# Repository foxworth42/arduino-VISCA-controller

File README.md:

# Arduino VISCA Controller

## The project is a work-in-progress

This is a project for using an Arduino to send VISCA commands.  This is tailored for interfacing with the
Cisco TelePresence PrecisionHD series of conference cameras (specifically testing with the TTC8-02 12x zoom w/ SDI output).

The TelePresence cameras have a slight quirk to controlling it over VISCA.  To get manual control over the pan/tilt/zoom
rates the camera needs to be sent the IR disable command, otherwise all movements behave with a speed ramp as if you 
were controlling it with an IR remote.

The Arduino Shield board present in the EAGLE directory is intended to make connecting to a TelePresence camera and
wiring I/O easier.  The shield has headers to allow for powering the Arduino off its internal voltage regulator or via
VIN (includes header points to make swapping easy).  There is also a header to provide 12v power over the RJ45
connection to remotely power the camera.  The shield incudes an RS232 transciever so it is ready to plug into the
camera's control port with a standard ethernet cable.

[Cisco TelePresence PrecisionHD User Guide](https://www.cisco.com/c/dam/en/us/td/docs/telepresence/endpoint/camera/precisionhd/user_guide/precisionhd_1080p-720p_camera_user_guide.pdf) (includes supported VISCA command details, cable wiring, etc.)

# Arduino Shield components

|Component|Quantity|Notes|Link|
|---|---|---|---|
|Arduino Shield|1|See EAGLE directory|[Link](https://oshpark.com/shared_projects/oP5dpPBc)|
|RS232 Transciever|1| |[Link](https://www.mouser.com/ProductDetail/968-HIN202IBNZ-T/)|
|0.1uf SMD Capacitor|5| |[Link](https://www.mouser.com/ProductDetail/80-C0805C104J5R/)|
|RJ45 Jack|1| |[Link](https://www.mouser.com/ProductDetail/523-RJHSE-5381/)|
|2pin Molex Header|2|Or whatever header you prefer|[Link](https://www.mouser.com/ProductDetail/538-22-23-2021/)|
|2pin Molex Housing|2| |[Link](https://www.mouser.com/ProductDetail/538-22-01-3027/)|
|3pin Molex Header|4| |[Link](https://www.mouser.com/ProductDetail/538-22-23-2031/)|
|3pin Molex Housing|4| |[Link](https://www.mouser.com/ProductDetail/538-22-01-3037/)|
|4pin Molex Header|2| |[Link](https://www.mouser.com/ProductDetail/538-22-23-2041/)|
|4pin Molex Housing|2| |[Link](https://www.mouser.com/ProductDetail/538-22-01-3047/)|
|8pin Molex Header|2| |[Link](https://www.mouser.com/ProductDetail/538-22-23-2081/)|
|8pin Molex Housing|2| |[Link](https://www.mouser.com/ProductDetail/538-22-01-3087/)|
|Crimp contacts for Molex housings|Lots| |[Link](https://www.mouser.com/ProductDetail/538-08-51-0108-LP/)|
|Crimp tool for Molex contacts|1| |[Link](https://www.amazon.com/gp/product/B078WPT5M1/ref=ppx_yo_dt_b_search_asin_title?ie=UTF8&psc=1)|
|Bunch of single row 2.54 pitch pin headers|Bunch| | |
|10k Ohm Resistors|10| |

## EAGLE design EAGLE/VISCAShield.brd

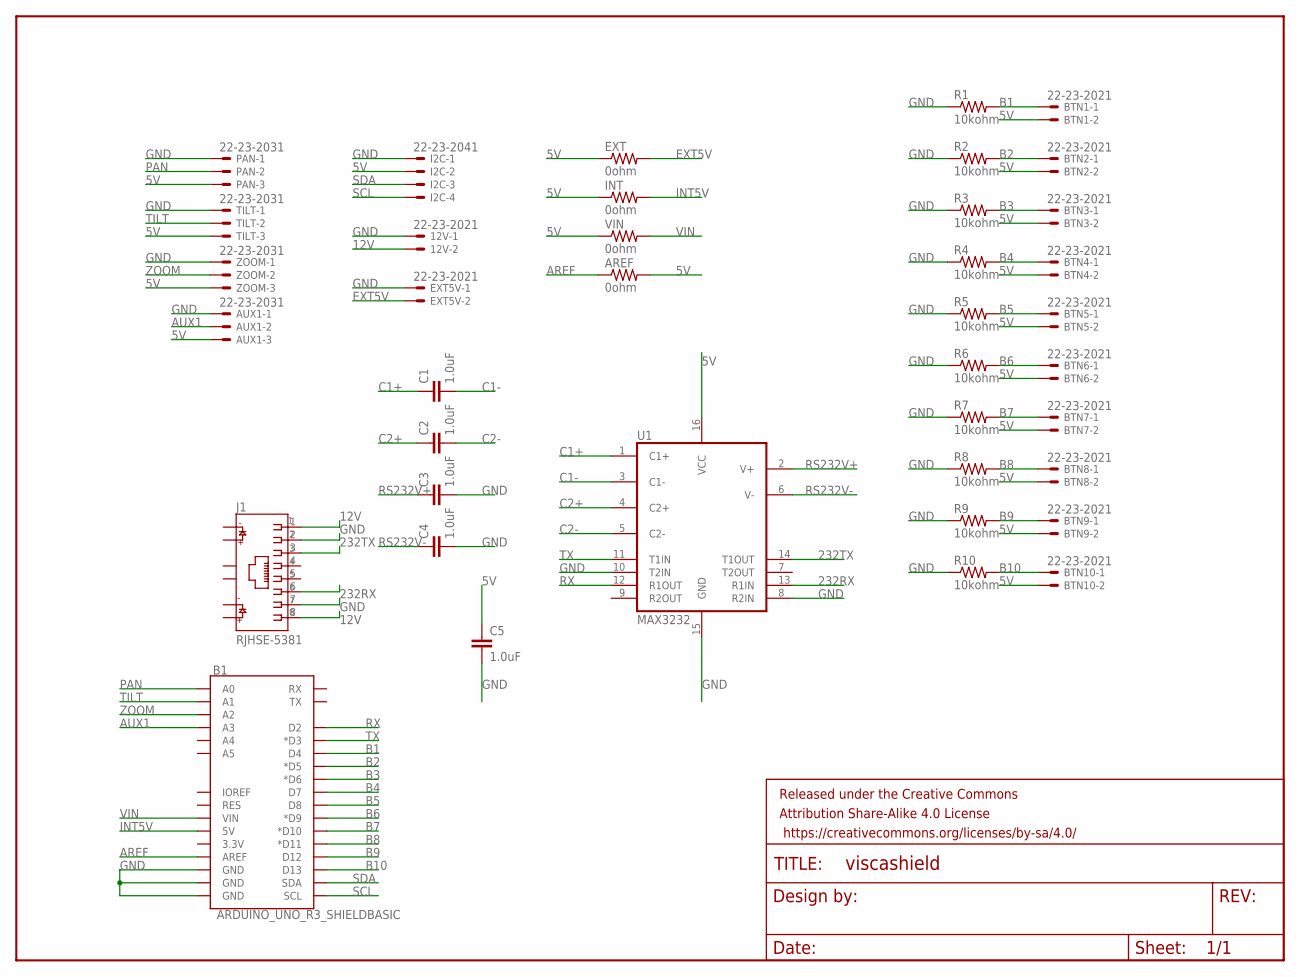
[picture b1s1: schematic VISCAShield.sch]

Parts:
12V: 22-23-2021
AREF: 0ohm; 0204V
AUX1: 22-23-2031
B1: ARDUINO_UNO_R3_SHIELDBASIC; UNO_R3_SHIELD
BTN1, BTN2, BTN3, BTN4, BTN5, BTN6, BTN7, BTN8, BTN9, BTN10: 22-23-2021
C1, C2, C3, C4, C5: 1.0uF; 0805
EXT: 0ohm; 0204V
EXT5V: 22-23-2021
FRAME1: FRAME-LETTERNO_PACKAGE; DUMMY
I2C: 22-23-2041
INT: 0ohm; 0204V
J1: RJHSE-5381; AMPHENOL_RJHSE-5381
PAN: 22-23-2031
R1, R2, R3, R4, R5, R6, R7, R8, R9, R10: 10kohm; 0204V
TILT: 22-23-2031
U1: MAX3232; SO16
VIN: 0ohm; 0204V
ZOOM: 22-23-2031

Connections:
5V: AREF.2, AUX1.3, BTN1.2, BTN2.2, BTN3.2, BTN4.2, BTN5.2, BTN6.2, BTN7.2, BTN8.2, BTN9.2, BTN10.2, C5.1, EXT.1, I2C.2, INT.1, PAN.3, TILT.3, U1.16 (VCC), VIN.1, ZOOM.3
12V: 12V.2, J1.1, J1.8
232RX: J1.6, U1.13 (R1IN)
232TX: J1.3, U1.14 (T1OUT)
AREF: AREF.1, B1.AREF
AUX1: AUX1.2, B1.A3
B1: B1.D4, BTN1.1, R1.2
B2: B1.D5 (*D5), BTN2.1, R2.2
B3: B1.D6 (*D6), BTN3.1, R3.2
B4: B1.D7, BTN4.1, R4.2
B5: B1.D8, BTN5.1, R5.2
B6: B1.D9 (*D9), BTN6.1, R6.2
B7: B1.D10 (*D10), BTN7.1, R7.2
B8: B1.D11 (*D11), BTN8.1, R8.2
B9: B1.D12, BTN9.1, R9.2
B10: B1.D13, BTN10.1, R10.2
C1+: C1.1, U1.1 (C1+)
C1-: C1.2, U1.3 (C1-)
C2+: C2.1, U1.4 (C2+)
C2-: C2.2, U1.5 (C2-)
EXT5V: EXT.2, EXT5V.2
GND: 12V.1, AUX1.1, B1.GND@0 (GND), B1.GND@1 (GND), B1.GND@2 (GND), C3.2, C4.2, C5.2, EXT5V.1, I2C.1, J1.2, J1.7, PAN.1, R1.1, R2.1, R3.1, R4.1, R5.1, R6.1, R7.1, R8.1, R9.1, R10.1, TILT.1, U1.8 (R2IN), U1.10 (T2IN), U1.15 (GND), ZOOM.1
INT5V: B1.5V, INT.2
PAN: B1.A0, PAN.2
RS232V+: C3.1, U1.2 (V+)
RS232V-: C4.1, U1.6 (V-)
RX: B1.D2, U1.12 (R1OUT)
SCL: B1.SCL, I2C.4
SDA: B1.SDA, I2C.3
TILT: B1.A1, TILT.2
TX: B1.D3 (*D3), U1.11 (T1IN)
VIN: B1.VIN, VIN.2
ZOOM: B1.A2, ZOOM.2

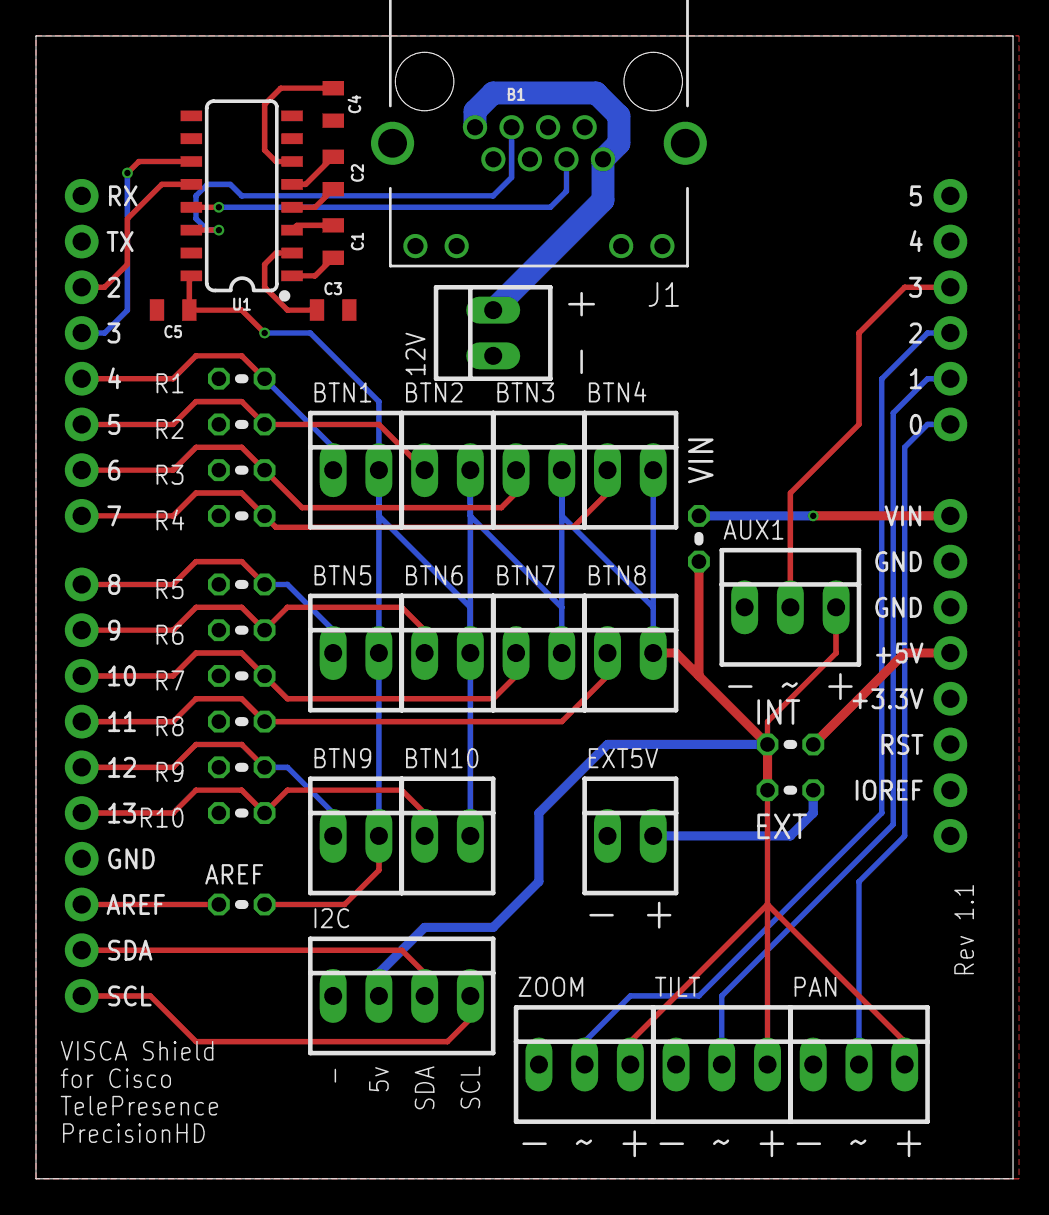
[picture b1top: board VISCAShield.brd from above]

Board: 2 copper layers, 54.3 x 63.5 mm, 40 parts (0 on the bottom side), 33 nets.

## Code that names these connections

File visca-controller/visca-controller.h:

#ifndef VISCACONTROLLER
#define VISCACONTROLLER

#include <Arduino.h>
#include <EEPROM.h>
//#include <LiquidCrystal_I2C.h>
#include <SoftwareSerial.h>

// Pin assignments from arduno shield.

// Analog inputs
#define PAN 0
#define TILT 1
#define ZOOM 2
#define AUX1 3
#define AUX2 4
#define AUX3 5

// Serial I/O for VISCA
#define VISCARX 2
#define VISCATX 3

// Button inputs
#define BTN1 4
#define BTN2 5
#define BTN3 6
#define BTN4 7
#define BTN5 8
#define BTN6 9
#define BTN7 10
#define BTN8 11
#define BTN9 12
#define BTN10 13
int buttons[] = {
  BTN1,
  BTN2,
  BTN3,
  BTN4,
  BTN5,
  BTN6,
  BTN7,
  BTN8,
  BTN9,
  BTN10
};


const byte numChars = 16;
byte viscaMessage[numChars];

byte buttonPreviousStatus = 0x00;
byte buttonCurrentStatus = 0x00;

// Pan/Tilt
byte panTilt[9] =       { 0x81, 0x01, 0x06, 0x01, 0x00, 0x00, 0x03, 0x03, 0xFF };
byte panUp[9] =         { 0x81, 0x01, 0x06, 0x01, 0x00, 0x00, 0x03, 0x01, 0xFF }; // 8x 01 06 01 0p 0t 03 01 ff
byte panDown[9] =       { 0x81, 0x01, 0x06, 0x01, 0x00, 0x00, 0x03, 0x02, 0xFF }; // 8x 01 06 01 0p 0t 03 02 ff
byte panLeft[9] =       { 0x81, 0x01, 0x06, 0x01, 0x00, 0x00, 0x01, 0x03, 0xFF }; // 8x 01 06 01 0p 0t 01 03 ff
byte panRight[9] =      { 0x81, 0x01, 0x06, 0x01, 0x00, 0x00, 0x02, 0x03, 0xFF }; // 8x 01 06 01 0p 0t 02 03 ff
byte panUpLeft[9] =     { 0x81, 0x01, 0x06, 0x01, 0x00, 0x00, 0x01, 0x01, 0xFF }; // 8x 01 06 01 0p 0t 01 01 ff
byte panUpRight[9] =    { 0x81, 0x01, 0x06, 0x01, 0x00, 0x00, 0x02, 0x01, 0xFF }; // 8x 01 06 01 0p 0t 02 01 ff
byte panDownLeft[9] =   { 0x81, 0x01, 0x06, 0x01, 0x00, 0x00, 0x01, 0x02, 0xFF }; // 8x 01 06 01 0p 0t 01 02 ff
byte panDownRight[9] =  { 0x81, 0x01, 0x06, 0x01, 0x00, 0x00, 0x02, 0x02, 0xFF }; // 8x 01 06 01 0p 0t 02 02 ff

byte panStop[9] =       { 0x81, 0x01, 0x06, 0x01, 0x09, 0x09, 0x03, 0x03, 0xFF }; // Camera Stop
byte panTiltPosReq[5] = { 0x81, 0x09, 0x06, 0x12, 0xff }; // Resp: y0 50 0p 0q 0r 0s 0t 0u 0v 0w ff ; pqrs: pan position ; tuvw: tilt position

// Zoom
// Tele: 8x 01 04 07 2p ff 
// Wide: 8x 01 04 07 2p ff 
byte zoom[6] =    { 0x81, 0x01, 0x04, 0x07, 0x2F, 0xff }; // 8x 01 04 07 2p ff 
byte zoomTele[6] =    { 0x81, 0x01, 0x04, 0x07, 0x2F, 0xff }; // 8x 01 04 07 2p ff 
byte zoomWide[6] =    { 0x81, 0x01, 0x04, 0x07, 0x3F, 0xff }; // 8x 01 04 07 3p ff
byte zoomStop[6] =    { 0x81, 0x01, 0x04, 0x07, 0x00, 0xff };
byte zoomDirect[9] =  { 0x81, 0x01, 0x04, 0x47, 0x00, 0x00, 0x00, 0x00, 0xff }; // 8x 01 04 47 0p 0q 0r 0s ff pqrs: zoom position
byte zoomPosReq[5] =  { 0x81, 0x09, 0x04, 0x47, 0xff }; // Resp: y0 50 0p 0q 0r 0s ff 


// Focus
byte focusAuto[6] =     { 0x81, 0x01, 0x04, 0x38, 0x02, 0xff };
byte focusManual[6] =   { 0x81, 0x01, 0x04, 0x38, 0x03, 0xff };
byte focusDirect[9] =   { 0x81, 0x01, 0x04, 0x48, 0x00, 0x00, 0x00, 0x00, 0xff }; // 8x 01 04 48 0p 0q 0r 0s ff pqrs: focus position
byte focusFar[6] =      { 0x81, 0x01, 0x04, 0x08, 0x20, 0xff };
byte focusNear[6] =     { 0x81, 0x01, 0x04, 0x08, 0x30, 0xff };
byte focusStop[6] =     { 0x81, 0x01, 0x04, 0x08, 0x00, 0xff };
byte focusModeInq[5] =  { 0x81, 0x09, 0x04, 0x38, 0xff }; // Resp: y0 50 0p ff ; p=2: Auto, p=3: Manual

// Iris / Gain
byte aeAuto[6] =      { 0x81, 0x01, 0x04, 0x39, 0x00, 0xff };
byte aeManual[6] =    { 0x81, 0x01, 0x04, 0x39, 0x03, 0xff };
byte irisDirect[9] =  { 0x81, 0x01, 0x04, 0x4B, 0x00, 0x00, 0x00, 0x00, 0xff }; // 8x 01 04 4B 0p 0q 0r 0s ff pqrs: Iris position, range 0..50
byte gainDirect[9] =  { 0x81, 0x01, 0x04, 0x4C, 0x00, 0x00, 0x00, 0x00, 0xff }; // 8x 01 04 4c 0p 0q 0r 0s ff pqrs: Gain position, values: 12-21dB.
byte aeModeInq[5] =   { 0x81, 0x09, 0x04, 0x39, 0xff }; // Resp: y0 50 0p ff ; p=0: Auto, p=3: Manual

// White Balance
byte wbAuto[6] =        { 0x81, 0x01, 0x04, 0x35, 0x00, 0xff };
byte wbTableManual[6] = { 0x81, 0x01, 0x04, 0x35, 0x06, 0xff };
byte wbTableDirect[9] = { 0x81, 0x01, 0x04, 0x75, 0x00, 0x00, 0x0, 0x00, 0xff }; // 8x 01 04 75 0p 0q 0r 0s ff pqrs = wb table.

// Config
byte address_command[4] = { 0x88, 0x30, 0x01, 0xFF }; // Sets camera address (Needed for Daisy Chaining)
byte if_clear[5] =        { 0x88, 0x01, 0x00, 0x01, 0xFF }; // Checks to see if communication line is clear
byte ir_off[6] =          { 0x81, 0x01, 0x06, 0x09, 0x03, 0xff }; // Turn off IR control (required for speed control of Pan/Tilt on TelePresence cameras)
byte callLedOn[6] =     { 0x81, 0x01, 0x33, 0x01, 0x01, 0xff};
byte callLedOff[6] =    { 0x81, 0x01, 0x33, 0x01, 0x00, 0xff};
byte callLedBlink[6] =  { 0x81, 0x01, 0x33, 0x01, 0x02, 0xff};

int delayTime = 500;  //Time between commands

void sendViscaPacket(byte* packet, int byteSize, bool echoCommand = true, bool sendPacket = true);

#endif

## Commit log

2020-01-04 Initial commit of arduino shield design.
    VISCA shield that exposes all pins to headers ready to be wired to 10 buttons,
    6 pots, I2C, with the option for external 5v, as well as an RJ45 jack wired
    for connecting to Cisco PrecisionHD PTZ cameras.
2020-01-04 initial commit of arduino sketch for VISCA controller.
2020-01-04 Add some quick comments about what the definitions are for.
2020-01-12 Some revisions.
2020-01-12 Remove I2C display for now until I start to make use of it.
2020-01-12 Add more axid movements, add focus control.
2020-01-12 Change return back.
2020-01-13 Add optional AREF input jumper. Clean up unused nets from schematic.
2021-01-17 Successful build of Visca shield & more testing of control code.
2021-01-17 Add README.
2021-01-17 Some cleanup.
2021-01-18 Minor update after further testing.
2021-01-18 Increase trace width on 12v power to RJ45 jack.
2021-01-18 Add BOM for shield.
2021-01-18 More gooder words
2021-01-19 Some cleanup and refactoring.
2021-01-19 Update part link, and some more cleanup.
2021-01-20 Refactor to C++ structure.
2021-01-20 More restructuring to edit code in a CLion/platform.io environment.
    I wanted to use a more featureful code editor.
2021-01-20 Add another README.
2021-01-20 Add note about opening Arduino code in the Arduino editor.
2021-01-20 Add jetbrains post link.
2021-01-20 Run code through formatter to clean things up.
2021-01-20 Narrow var scopes.
2021-01-23 Add automatic analog control zero point/movement calibration & more cleanup/refinement.
2021-01-23 Fix issue with not being able to pan/tilt at the slowest possible speed.
2021-01-24 Not sure why this was here...
2021-01-30 Add note to README.
2021-02-06 WIP checkin of extracting VISCA communication to separate class.
2021-02-06 Add video format to camera initialization.

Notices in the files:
parts and their libraries:
SparkFun-Boards: Licensing: Creative Commons ShareAlike 4.0 International - https://creativecommons.org/licenses/by-sa/4.0
SparkFun-Aesthetics: Released under the Creative Commons Attribution Share-Alike 4.0 License
SparkFun-Aesthetics: https://creativecommons.org/licenses/by-sa/4.0
